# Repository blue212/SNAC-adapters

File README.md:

# SNAC-adapters
Various adapters for use with SNAC

For use with the USB3 version of SNAC

-Updates

Changed the partslist to use a different part for the male USB connector.

Uxcell a19032000ux0260 instead of Wuerth 692112030100

Added nes2p, snes2p, famicom boards. 

Added an experimental board tg16 buffer board, fixes turbo on 2 button pads

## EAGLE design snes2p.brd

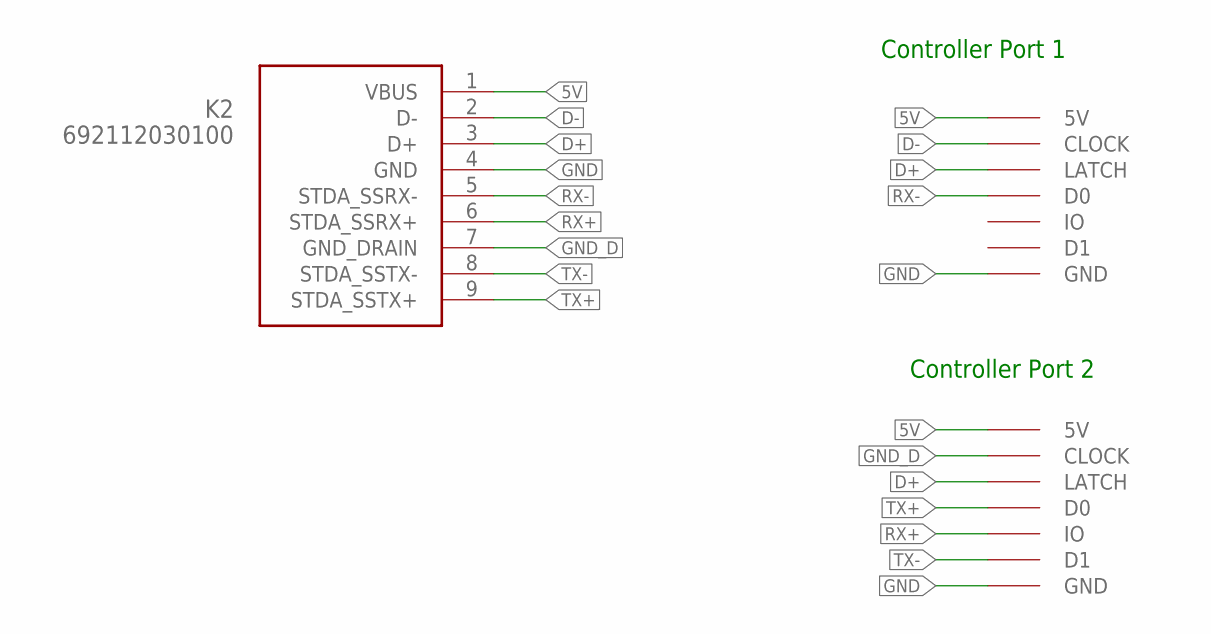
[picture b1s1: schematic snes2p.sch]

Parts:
K2: 692112030100
U$1, U$2: SNESCONN

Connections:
5V: K2.1 (VBUS), U$1.5V, U$2.5V
D+: K2.3 (D+), U$1.LATCH, U$2.LATCH
D-: K2.2 (D-), U$1.CLOCK
GND: K2.4 (GND), U$1.GND, U$2.GND
GND_D: K2.7 (GND_DRAIN), U$2.CLOCK
RX+: K2.6 (STDA_SSRX+), U$2.IO
RX-: K2.5 (STDA_SSRX-), U$1.D0
TX+: K2.9 (STDA_SSTX+), U$2.D0
TX-: K2.8 (STDA_SSTX-), U$2.D1

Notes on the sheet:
Controller Port 2
Controller Port 1

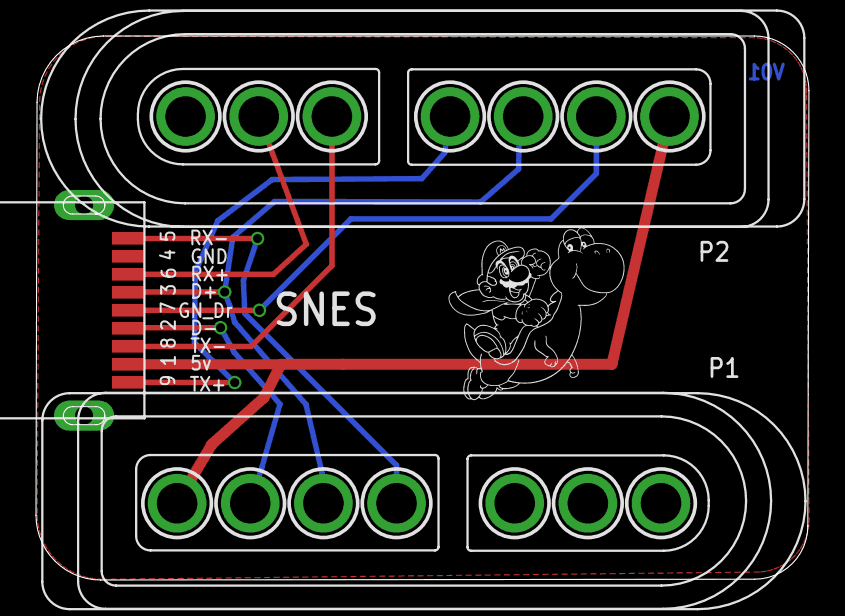
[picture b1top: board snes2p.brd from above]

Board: 2 copper layers, 42.9 x 30.2 mm, 3 parts (0 on the bottom side), 9 nets.

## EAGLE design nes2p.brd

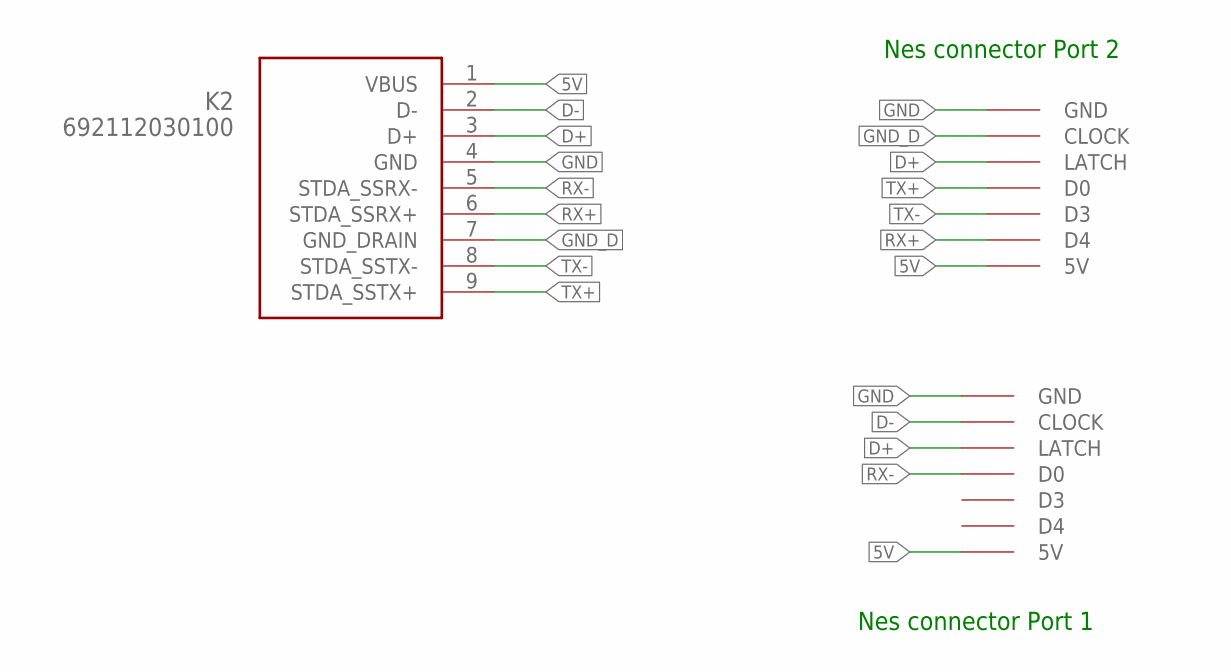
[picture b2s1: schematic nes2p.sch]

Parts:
K2: 692112030100
U$1, U$2: NESCONNNO_TABS; NESCONN_NO_TABS

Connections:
5V: K2.1 (VBUS), U$1.5V, U$2.5V
D+: K2.3 (D+), U$1.LATCH, U$2.LATCH
D-: K2.2 (D-), U$2.CLOCK
GND: K2.4 (GND), U$1.GND, U$2.GND
GND_D: K2.7 (GND_DRAIN), U$1.CLOCK
RX+: K2.6 (STDA_SSRX+), U$1.D4
RX-: K2.5 (STDA_SSRX-), U$2.D0
TX+: K2.9 (STDA_SSTX+), U$1.D0
TX-: K2.8 (STDA_SSTX-), U$1.D3

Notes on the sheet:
Nes connector Port 2
Nes connector Port 1

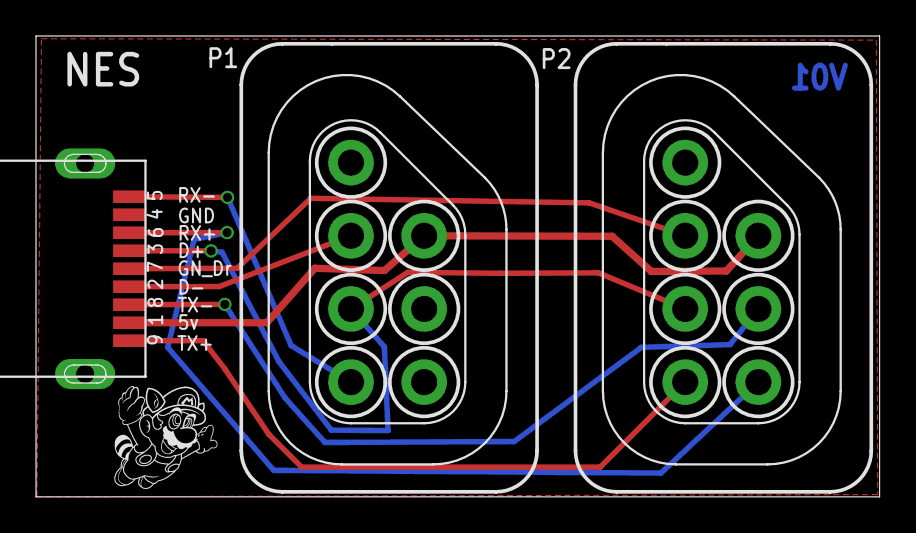
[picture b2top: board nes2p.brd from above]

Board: 2 copper layers, 46.9 x 25.6 mm, 3 parts (0 on the bottom side), 9 nets.

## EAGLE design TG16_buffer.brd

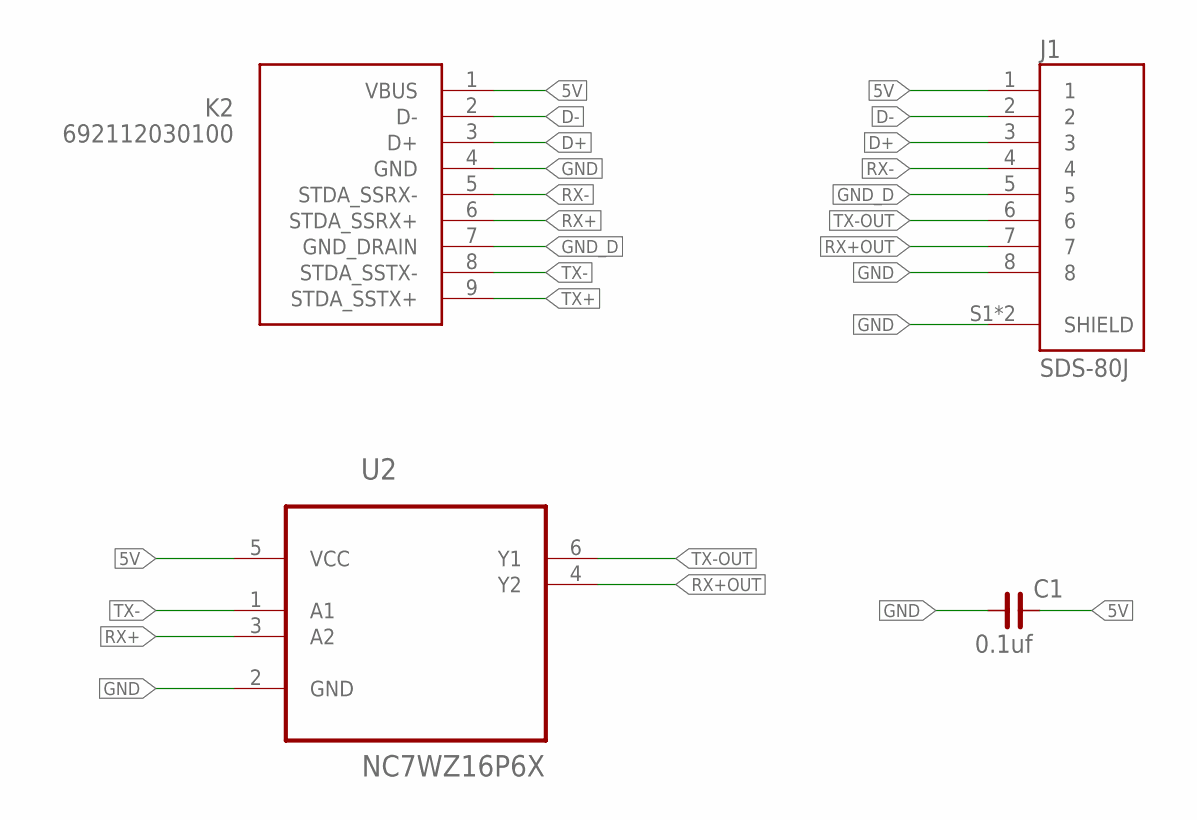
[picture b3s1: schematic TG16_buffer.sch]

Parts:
C1: 0.1uf; C0805
J1: SDS-80J; CUI_SDS-80J
K2: 692112030100
U2: NC7WZ16P6X; SOT65P210X110-6N

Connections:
5V: C1.2, J1.1, K2.1 (VBUS), U2.5 (VCC)
D+: J1.3, K2.3 (D+)
D-: J1.2, K2.2 (D-)
GND: C1.1, J1.8, J1.S1 (SHIELD), J1.S2 (SHIELD), K2.4 (GND), U2.2 (GND)
GND_D: J1.5, K2.7 (GND_DRAIN)
RX+: K2.6 (STDA_SSRX+), U2.3 (A2)
RX+OUT: J1.7, U2.4 (Y2)
RX-: J1.4, K2.5 (STDA_SSRX-)
TX+: K2.9 (STDA_SSTX+)
TX-: K2.8 (STDA_SSTX-), U2.1 (A1)
TX-OUT: J1.6, U2.6 (Y1)

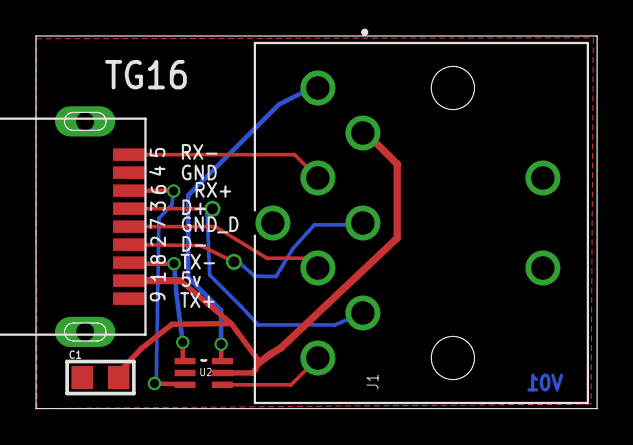
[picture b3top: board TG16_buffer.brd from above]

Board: 2 copper layers, 31.2 x 20.7 mm, 4 parts (0 on the bottom side), 10 nets.

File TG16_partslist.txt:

Partlist

Part     Value          Package      Library                                                  Position (inch)       Orientation

J1       SDS-80J        CUI_SDS-80J  SDS-80J                                                  (0.712 0.407)         R90
K2       a19032000ux0260   a19032000ux0260 Uxcell                                             (0.201 0.399)         R90

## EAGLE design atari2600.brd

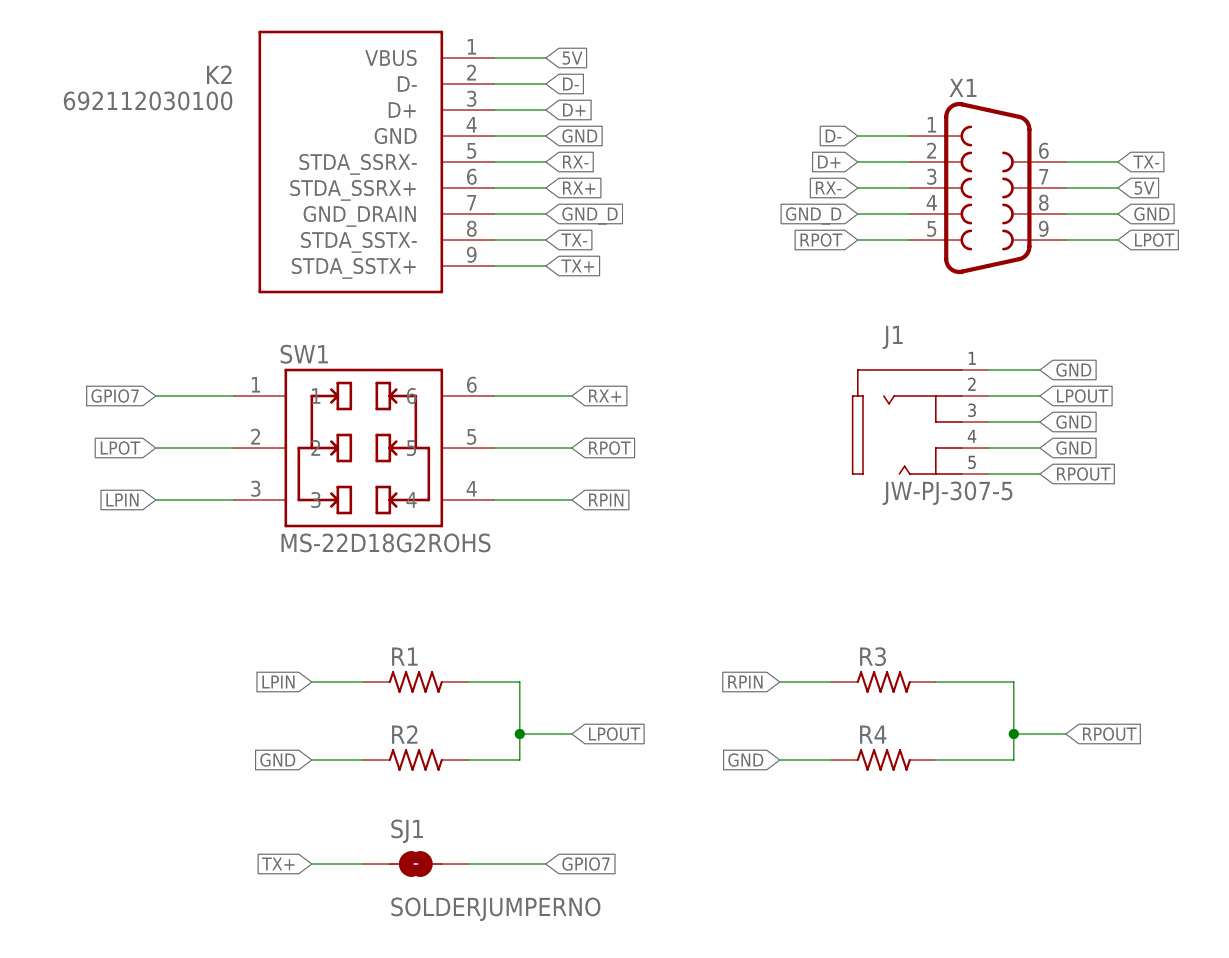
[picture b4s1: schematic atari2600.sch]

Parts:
J1: JW-PJ-307-5; JW-PJ-307-X
K2: 692112030100
R1, R2, R3, R4: R_0603; R0603
SJ1: SOLDERJUMPERNO; SJ_2S-NO
SW1: MS-22D18G2ROHS; SW_MS-22D18G2ROHS
X1: DB9MALE; DB9_MALE

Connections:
5V: K2.1 (VBUS), X1.7
D+: K2.3 (D+), X1.2
D-: K2.2 (D-), X1.1
GND: J1.P$1 (1), J1.P$3 (3), J1.P$4 (4), K2.4 (GND), R2.1, R4.1, X1.8
GND_D: K2.7 (GND_DRAIN), X1.4
GPIO7: SJ1.2, SW1.1
LPIN: R1.1, SW1.3
LPOT: SW1.2, X1.9
LPOUT: J1.P$2 (2), R1.2, R2.2
RPIN: R3.1, SW1.4
RPOT: SW1.5, X1.5
RPOUT: J1.P$5 (5), R3.2, R4.2
RX+: K2.6 (STDA_SSRX+), SW1.6
RX-: K2.5 (STDA_SSRX-), X1.3
TX+: K2.9 (STDA_SSTX+), SJ1.1
TX-: K2.8 (STDA_SSTX-), X1.6

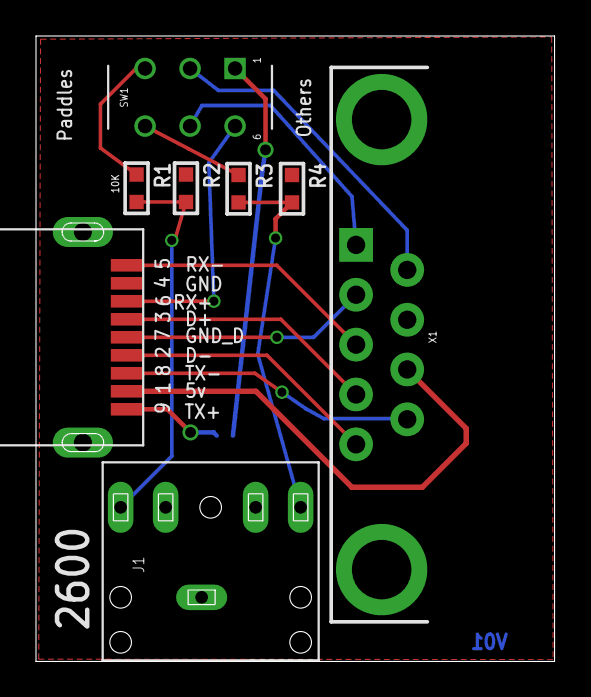
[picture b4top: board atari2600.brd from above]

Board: 2 copper layers, 28.8 x 34.7 mm, 9 parts (1 on the bottom side), 16 nets.

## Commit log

2022-08-16 Added nes2p, snes2p, famicom, tg16b boards

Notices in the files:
parts and their libraries:
Wuerth_Elektronik_eiCan_Communication_Co: Copyright: Würth Elektronik
rc-master-smd: Copyright (C) 2007, Bob Starr
SparkFun: Licensing: CC v3.0 Share-Alike You are welcome to use this library for commercial purposes.
